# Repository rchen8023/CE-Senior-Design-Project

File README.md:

# CE-Senior-Design-Project

This project aims to create and design an independent IoT system allowing users to open and close their household vertical blinds with just a simple tap on their personal mobile phones or tablets. The project requires three parts involving the software, hardware, and mechanical developments. The software aspect involves a web application which allows the user to open or close the blinds as they wish. The web application communicates to the hardware unit via WiFi where the user data is received by the System On Chip (SoC), ESP8266. The ESP8266 can then send out PWM signals to the stepper motor which along with the mechanical design is able to physically move the window blinds. The web application is implemented using HTML and CSS styling uploaded to the ESP8266 web server. The ESP8266 is programmed using the Arduino IDE, and the mechanical design independently sketched and designed using Tinkercad

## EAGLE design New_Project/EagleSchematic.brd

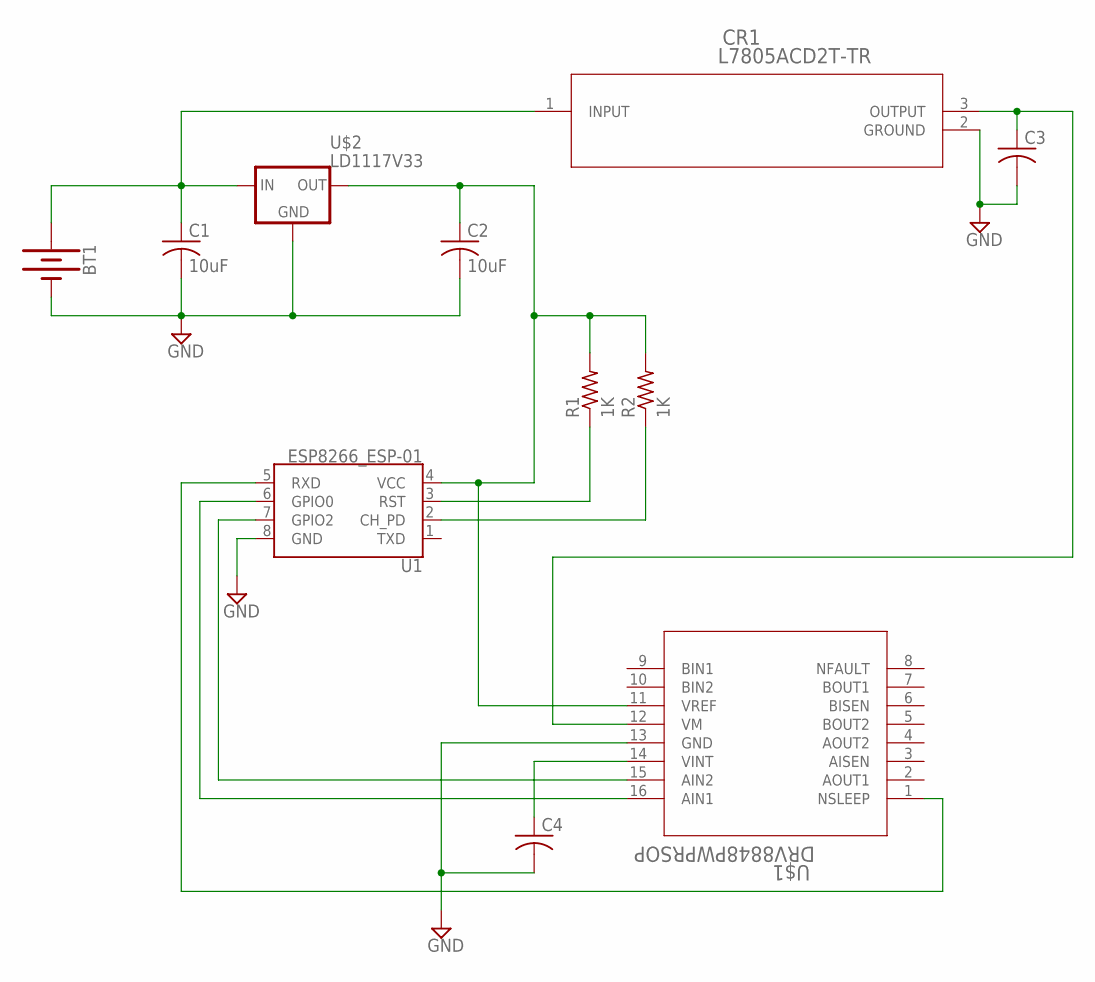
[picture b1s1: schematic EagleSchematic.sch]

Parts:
BT1: BATTERY-9V; BATTCON_9V
C1, C2: 10uF; C025-024X044
C3, C4: C-US025-024X044; C025-024X044
CR1: L7805ACD2T-TR; D2PAK
R1, R2: 1K; 0204/5
U1: ESP8266_ESP-01
U$1: DRV8848PWPRSOP; SOIC127P1032X265-16
U$2: LD1117V33

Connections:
3.3V: C2.1, R1.2, R2.2, U1.4 (VCC), U$1.11 (VREF), U$2.OUT
GND: C3.2, C4.2, CR1.2 (GROUND), U1.8 (GND), U$1.13 (GND)
unnamed: BT1.+, C1.1, CR1.1 (INPUT), U$2.IN
unnamed: BT1.-, C1.2, C2.2, U$2.GND
unnamed: C4.1, U$1.14 (VINT)
unnamed: R1.1, U1.3 (RST)
unnamed: R2.1, U1.2 (CH_PD)
unnamed: C3.1, CR1.3 (OUTPUT), U$1.12 (VM)
unnamed: U1.7 (GPIO2), U$1.15 (AIN2)
unnamed: U1.6 (GPIO0), U$1.16 (AIN1)
unnamed: U1.5 (RXD), U$1.1 (NSLEEP)

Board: 2 copper layers, 11 parts (0 on the bottom side), 11 nets, no tracks yet.

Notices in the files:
parts and their libraries:
SparkFun-RF: Licensing: Creative Commons ShareAlike 4.0 International - https://creativecommons.org/licenses/by-sa/4.0
